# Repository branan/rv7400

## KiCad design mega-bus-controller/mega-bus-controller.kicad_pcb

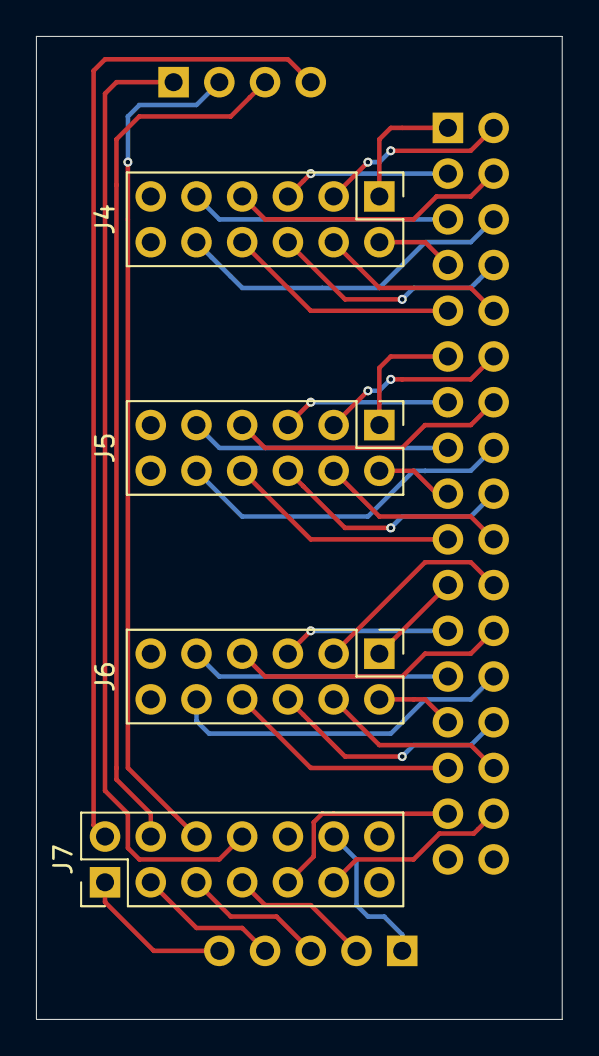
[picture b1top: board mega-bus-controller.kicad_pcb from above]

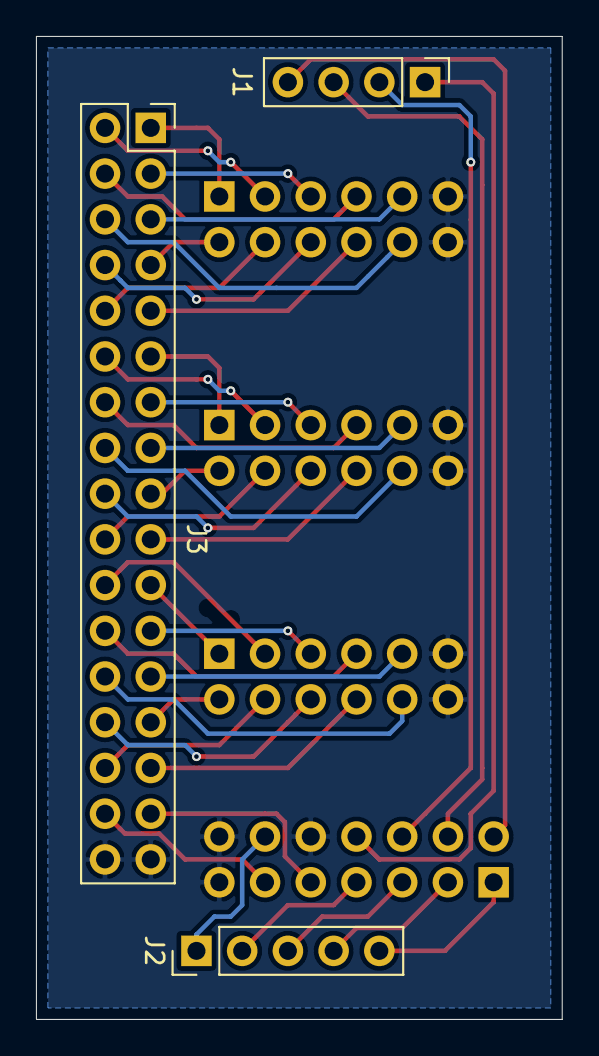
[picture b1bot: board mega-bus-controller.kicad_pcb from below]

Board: 2 copper layers, 29.2 x 54.6 mm, 7 parts (3 on the bottom side), 42 nets.

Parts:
J1: Conn_01x04; PinHeader_1x04_P2.54mm_Vertical
J2: Conn_01x05; PinHeader_1x05_P2.54mm_Vertical
J3: Conn_02x17_Odd_Even; PinHeader_2x17_P2.54mm_Vertical
J4, J5, J6: Conn_02x06_Odd_Even; PinHeader_2x06_P2.54mm_Vertical
J7: Conn_02x07_Odd_Even; PinHeader_2x07_P2.54mm_Vertical

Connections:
/AR0: J3.1, J4.1
/AR1: J3.2, J4.3
/AR2: J3.3, J4.5
/AR3: J3.4, J4.7
/AR4: J3.5, J4.9
/BR0: J3.11, J5.1
/BR1: J3.12, J5.3
/BR2: J3.13, J5.5
/BR3: J3.14, J5.7
/BR4: J3.15, J5.9
/CLK: J2.1, J7.12
/CLK_A: J3.8, J4.6
/CLK_B: J3.18, J5.6
/CLK_Y: J3.28, J6.6
/CTRL_A6: J1.2, J7.6
/CTRL_B5: J1.1, J7.8
/CTRL_B6: J1.3, J7.4
/CTRL_B22: J1.4, J7.2
/DIN_A: J3.6, J4.10
/DIN_B: J3.16, J5.10
/DIN_Y: J3.26, J6.10
/DOUT_A: J3.7, J4.2
/DOUT_B: J3.17, J5.2
/DOUT_Y: J3.27, J6.2
/FUNC0: J2.5, J7.1
/FUNC1: J2.4, J7.3
/FUNC2: J2.3, J7.5
/IMM10: J2.2, J7.7
/MR: J3.31, J7.9
/MW: J3.32, J7.11
/YR0: J3.21, J6.1
/YR1: J3.22, J6.3
/YR2: J3.23, J6.5
/YR3: J3.24, J6.7
/YR4: J3.25, J6.9
/~OE_A: J3.9, J4.8
/~OE_B: J3.19, J5.8
/~OE_Y: J3.29, J6.8
/~SHIFT_A~|LOAD_A: J3.10, J4.4
/~SHIFT_B~|LOAD_B: J3.20, J5.4
/~SHIFT_Y~|LOAD_Y: J3.30, J6.4
GND: J3.33, J3.34, J4.11, J4.12, J5.11, J5.12, J6.11, J6.12, J7.10, J7.13, J7.14

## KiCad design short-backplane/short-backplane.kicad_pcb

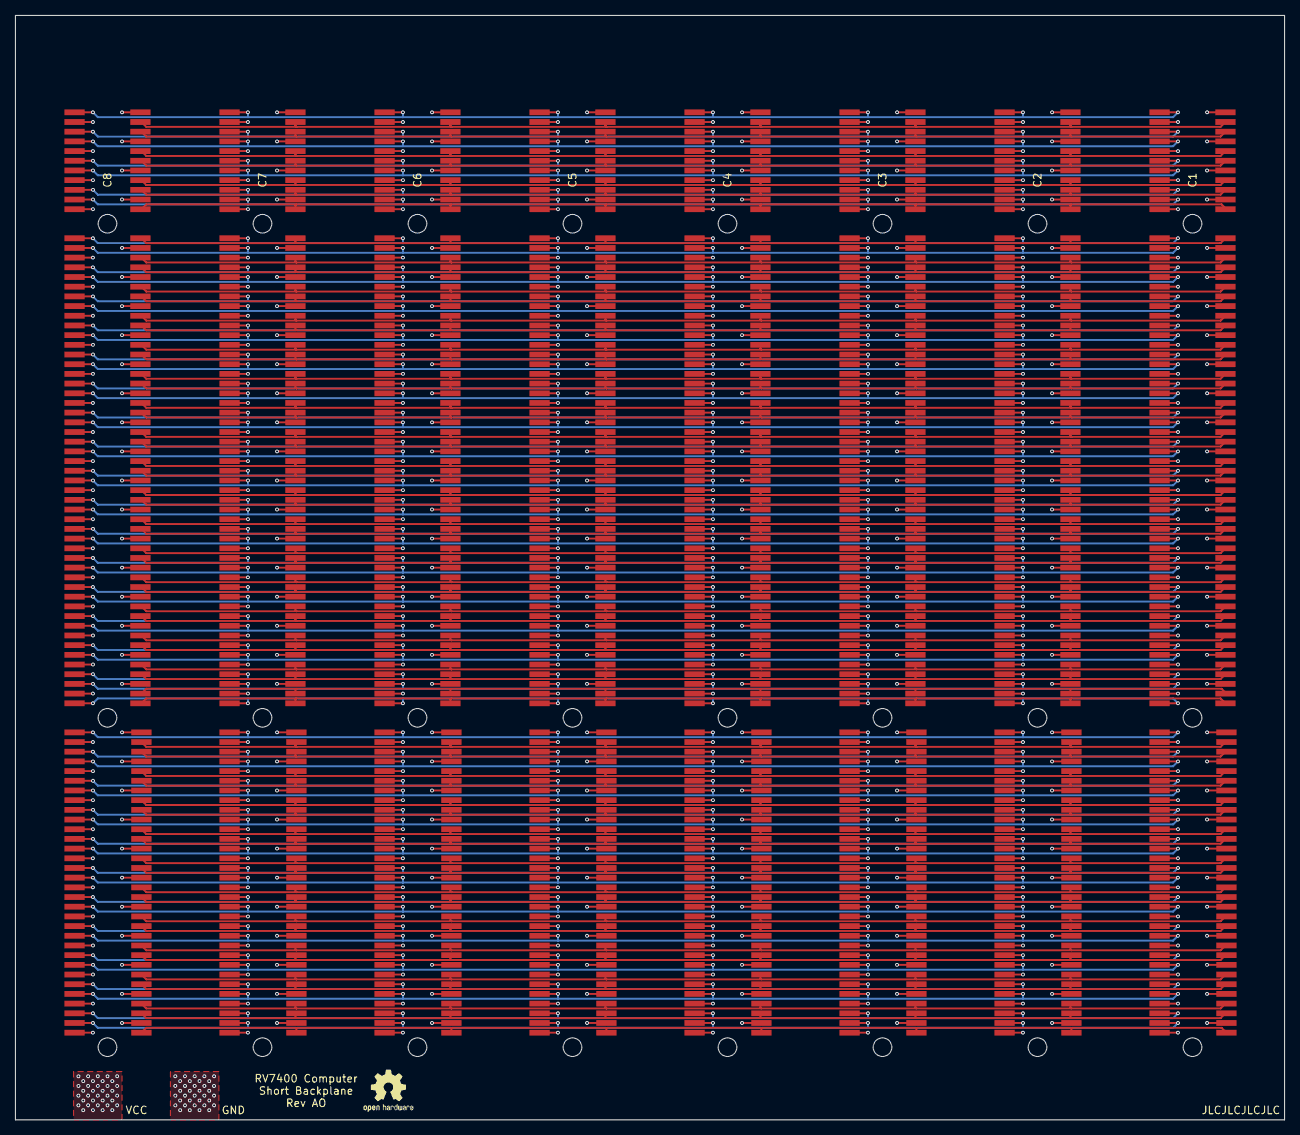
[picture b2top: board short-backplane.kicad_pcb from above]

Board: 4 copper layers, 166.4 x 144.8 mm, 8 parts (0 on the bottom side), 124 nets.

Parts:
C1, C2, C3, C4, C5, C6, C7, C8: Bus; PCI-X Backplane

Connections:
/A0: C1.A23, C2.A23, C3.A23, C4.A23, C5.A23, C6.A23, C7.A23, C8.A23
/A1: C1.B23, C2.B23, C3.B23, C4.B23, C5.B23, C6.B23, C7.B23, C8.B23
/A2: C1.A24, C2.A24, C3.A24, C4.A24, C5.A24, C6.A24, C7.A24, C8.A24
/A3: C1.B25, C2.B25, C3.B25, C4.B25, C5.B25, C6.B25, C7.B25, C8.B25
/A4: C1.A26, C2.A26, C3.A26, C4.A26, C5.A26, C6.A26, C7.A26, C8.A26
/A5: C1.B26, C2.B26, C3.B26, C4.B26, C5.B26, C6.B26, C7.B26, C8.B26
/A6: C1.A27, C2.A27, C3.A27, C4.A27, C5.A27, C6.A27, C7.A27, C8.A27
/A7: C1.B28, C2.B28, C3.B28, C4.B28, C5.B28, C6.B28, C7.B28, C8.B28
/A8: C1.A29, C2.A29, C3.A29, C4.A29, C5.A29, C6.A29, C7.A29, C8.A29
/A9: C1.B29, C2.B29, C3.B29, C4.B29, C5.B29, C6.B29, C7.B29, C8.B29
/A10: C1.A30, C2.A30, C3.A30, C4.A30, C5.A30, C6.A30, C7.A30, C8.A30
/A11: C1.B31, C2.B31, C3.B31, C4.B31, C5.B31, C6.B31, C7.B31, C8.B31
/A12: C1.A32, C2.A32, C3.A32, C4.A32, C5.A32, C6.A32, C7.A32, C8.A32
/A13: C1.B32, C2.B32, C3.B32, C4.B32, C5.B32, C6.B32, C7.B32, C8.B32
/A14: C1.A33, C2.A33, C3.A33, C4.A33, C5.A33, C6.A33, C7.A33, C8.A33
/A15: C1.B34, C2.B34, C3.B34, C4.B34, C5.B34, C6.B34, C7.B34, C8.B34
/A16: C1.A35, C2.A35, C3.A35, C4.A35, C5.A35, C6.A35, C7.A35, C8.A35
/A17: C1.B35, C2.B35, C3.B35, C4.B35, C5.B35, C6.B35, C7.B35, C8.B35
/A18: C1.A36, C2.A36, C3.A36, C4.A36, C5.A36, C6.A36, C7.A36, C8.A36
/A19: C1.B37, C2.B37, C3.B37, C4.B37, C5.B37, C6.B37, C7.B37, C8.B37
/A20: C1.A38, C2.A38, C3.A38, C4.A38, C5.A38, C6.A38, C7.A38, C8.A38
/A21: C1.B38, C2.B38, C3.B38, C4.B38, C5.B38, C6.B38, C7.B38, C8.B38
/A22: C1.A39, C2.A39, C3.A39, C4.A39, C5.A39, C6.A39, C7.A39, C8.A39
/A23: C1.B40, C2.B40, C3.B40, C4.B40, C5.B40, C6.B40, C7.B40, C8.B40
/A24: C1.A41, C2.A41, C3.A41, C4.A41, C5.A41, C6.A41, C7.A41, C8.A41
/A25: C1.B41, C2.B41, C3.B41, C4.B41, C5.B41, C6.B41, C7.B41, C8.B41
/A26: C1.A42, C2.A42, C3.A42, C4.A42, C5.A42, C6.A42, C7.A42, C8.A42
/A27: C1.B43, C2.B43, C3.B43, C4.B43, C5.B43, C6.B43, C7.B43, C8.B43
/A28: C1.A44, C2.A44, C3.A44, C4.A44, C5.A44, C6.A44, C7.A44, C8.A44
/A29: C1.B44, C2.B44, C3.B44, C4.B44, C5.B44, C6.B44, C7.B44, C8.B44
/A30: C1.A45, C2.A45, C3.A45, C4.A45, C5.A45, C6.A45, C7.A45, C8.A45
/A31: C1.B46, C2.B46, C3.B46, C4.B46, C5.B46, C6.B46, C7.B46, C8.B46
/AR0: C1.A1, C2.A1, C3.A1, C4.A1, C5.A1, C6.A1, C7.A1, C8.A1
/AR1: C1.B2, C2.B2, C3.B2, C4.B2, C5.B2, C6.B2, C7.B2, C8.B2
/AR2: C1.A3, C2.A3, C3.A3, C4.A3, C5.A3, C6.A3, C7.A3, C8.A3
/AR3: C1.B3, C2.B3, C3.B3, C4.B3, C5.B3, C6.B3, C7.B3, C8.B3
/AR4: C1.A4, C2.A4, C3.A4, C4.A4, C5.A4, C6.A4, C7.A4, C8.A4
/B0: C1.A47, C2.A47, C3.A47, C4.A47, C5.A47, C6.A47, C7.A47, C8.A47
/B1: C1.B47, C2.B47, C3.B47, C4.B47, C5.B47, C6.B47, C7.B47, C8.B47
/B2: C1.A48, C2.A48, C3.A48, C4.A48, C5.A48, C6.A48, C7.A48, C8.A48
/B3: C1.B49, C2.B49, C3.B49, C4.B49, C5.B49, C6.B49, C7.B49, C8.B49
/B4: C1.A50, C2.A50, C3.A50, C4.A50, C5.A50, C6.A50, C7.A50, C8.A50
/B5: C1.B50, C2.B50, C3.B50, C4.B50, C5.B50, C6.B50, C7.B50, C8.B50
/B6: C1.A51, C2.A51, C3.A51, C4.A51, C5.A51, C6.A51, C7.A51, C8.A51
/B7: C1.B52, C2.B52, C3.B52, C4.B52, C5.B52, C6.B52, C7.B52, C8.B52
/B8: C1.A53, C2.A53, C3.A53, C4.A53, C5.A53, C6.A53, C7.A53, C8.A53
/B9: C1.B53, C2.B53, C3.B53, C4.B53, C5.B53, C6.B53, C7.B53, C8.B53
/B10: C1.A54, C2.A54, C3.A54, C4.A54, C5.A54, C6.A54, C7.A54, C8.A54
/B11: C1.B55, C2.B55, C3.B55, C4.B55, C5.B55, C6.B55, C7.B55, C8.B55
/B12: C1.A56, C2.A56, C3.A56, C4.A56, C5.A56, C6.A56, C7.A56, C8.A56
/B13: C1.B56, C2.B56, C3.B56, C4.B56, C5.B56, C6.B56, C7.B56, C8.B56
/B14: C1.A57, C2.A57, C3.A57, C4.A57, C5.A57, C6.A57, C7.A57, C8.A57
/B15: C1.B58, C2.B58, C3.B58, C4.B58, C5.B58, C6.B58, C7.B58, C8.B58
/B16: C1.A59, C2.A59, C3.A59, C4.A59, C5.A59, C6.A59, C7.A59, C8.A59
/B17: C1.B59, C2.B59, C3.B59, C4.B59, C5.B59, C6.B59, C7.B59, C8.B59
/B18: C1.A60, C2.A60, C3.A60, C4.A60, C5.A60, C6.A60, C7.A60, C8.A60
/B19: C1.B61, C2.B61, C3.B61, C4.B61, C5.B61, C6.B61, C7.B61, C8.B61
/B20: C1.A62, C2.A62, C3.A62, C4.A62, C5.A62, C6.A62, C7.A62, C8.A62
/B21: C1.B62, C2.B62, C3.B62, C4.B62, C5.B62, C6.B62, C7.B62, C8.B62
/B22: C1.A65, C2.A65, C3.A65, C4.A65, C5.A65, C6.A65, C7.A65, C8.A65
/B23: C1.B66, C2.B66, C3.B66, C4.B66, C5.B66, C6.B66, C7.B66, C8.B66
/B24: C1.A67, C2.A67, C3.A67, C4.A67, C5.A67, C6.A67, C7.A67, C8.A67
/B25: C1.B67, C2.B67, C3.B67, C4.B67, C5.B67, C6.B67, C7.B67, C8.B67
/B26: C1.A68, C2.A68, C3.A68, C4.A68, C5.A68, C6.A68, C7.A68, C8.A68
/B27: C1.B69, C2.B69, C3.B69, C4.B69, C5.B69, C6.B69, C7.B69, C8.B69
/B28: C1.A70, C2.A70, C3.A70, C4.A70, C5.A70, C6.A70, C7.A70, C8.A70
/B29: C1.B70, C2.B70, C3.B70, C4.B70, C5.B70, C6.B70, C7.B70, C8.B70
/B30: C1.A71, C2.A71, C3.A71, C4.A71, C5.A71, C6.A71, C7.A71, C8.A71
/B31: C1.B72, C2.B72, C3.B72, C4.B72, C5.B72, C6.B72, C7.B72, C8.B72
/BR0: C1.A7, C2.A7, C3.A7, C4.A7, C5.A7, C6.A7, C7.A7, C8.A7
/BR1: C1.B8, C2.B8, C3.B8, C4.B8, C5.B8, C6.B8, C7.B8, C8.B8
/BR2: C1.A9, C2.A9, C3.A9, C4.A9, C5.A9, C6.A9, C7.A9, C8.A9
/BR3: C1.B9, C2.B9, C3.B9, C4.B9, C5.B9, C6.B9, C7.B9, C8.B9
/BR4: C1.A10, C2.A10, C3.A10, C4.A10, C5.A10, C6.A10, C7.A10, C8.A10
/CLK: C1.B11, C2.B11, C3.B11, C4.B11, C5.B11, C6.B11, C7.B11, C8.B11
/CTRL_A6: C1.A6, C2.A6, C3.A6, C4.A6, C5.A6, C6.A6, C7.A6, C8.A6
/CTRL_B5: C1.B5, C2.B5, C3.B5, C4.B5, C5.B5, C6.B5, C7.B5, C8.B5
/CTRL_B6: C1.B6, C2.B6, C3.B6, C4.B6, C5.B6, C6.B6, C7.B6, C8.B6
/CTRL_B22: C1.B22, C2.B22, C3.B22, C4.B22, C5.B22, C6.B22, C7.B22, C8.B22
/FUNC0: C1.A20, C2.A20, C3.A20, C4.A20, C5.A20, C6.A20, C7.A20, C8.A20
/FUNC1: C1.B20, C2.B20, C3.B20, C4.B20, C5.B20, C6.B20, C7.B20, C8.B20
/FUNC2: C1.A21, C2.A21, C3.A21, C4.A21, C5.A21, C6.A21, C7.A21, C8.A21
/IMM10: C1.B19, C2.B19, C3.B19, C4.B19, C5.B19, C6.B19, C7.B19, C8.B19
/MR: C1.A14, C2.A14, C3.A14, C4.A14, C5.A14, C6.A14, C7.A14, C8.A14
/MW: C1.B14, C2.B14, C3.B14, C4.B14, C5.B14, C6.B14, C7.B14, C8.B14
/Y0: C1.A73, C2.A73, C3.A73, C4.A73, C5.A73, C6.A73, C7.A73, C8.A73
/Y1: C1.B73, C2.B73, C3.B73, C4.B73, C5.B73, C6.B73, C7.B73, C8.B73
/Y2: C1.A74, C2.A74, C3.A74, C4.A74, C5.A74, C6.A74, C7.A74, C8.A74
/Y3: C1.B75, C2.B75, C3.B75, C4.B75, C5.B75, C6.B75, C7.B75, C8.B75
/Y4: C1.A76, C2.A76, C3.A76, C4.A76, C5.A76, C6.A76, C7.A76, C8.A76
/Y5: C1.B76, C2.B76, C3.B76, C4.B76, C5.B76, C6.B76, C7.B76, C8.B76
/Y6: C1.A77, C2.A77, C3.A77, C4.A77, C5.A77, C6.A77, C7.A77, C8.A77
/Y7: C1.B78, C2.B78, C3.B78, C4.B78, C5.B78, C6.B78, C7.B78, C8.B78
/Y8: C1.A79, C2.A79, C3.A79, C4.A79, C5.A79, C6.A79, C7.A79, C8.A79
/Y9: C1.B79, C2.B79, C3.B79, C4.B79, C5.B79, C6.B79, C7.B79, C8.B79
/Y10: C1.A80, C2.A80, C3.A80, C4.A80, C5.A80, C6.A80, C7.A80, C8.A80
/Y11: C1.B81, C2.B81, C3.B81, C4.B81, C5.B81, C6.B81, C7.B81, C8.B81
/Y12: C1.A82, C2.A82, C3.A82, C4.A82, C5.A82, C6.A82, C7.A82, C8.A82
/Y13: C1.B82, C2.B82, C3.B82, C4.B82, C5.B82, C6.B82, C7.B82, C8.B82
/Y14: C1.A83, C2.A83, C3.A83, C4.A83, C5.A83, C6.A83, C7.A83, C8.A83
/Y15: C1.B84, C2.B84, C3.B84, C4.B84, C5.B84, C6.B84, C7.B84, C8.B84
/Y16: C1.A85, C2.A85, C3.A85, C4.A85, C5.A85, C6.A85, C7.A85, C8.A85
/Y17: C1.B85, C2.B85, C3.B85, C4.B85, C5.B85, C6.B85, C7.B85, C8.B85
/Y18: C1.A86, C2.A86, C3.A86, C4.A86, C5.A86, C6.A86, C7.A86, C8.A86
/Y19: C1.B87, C2.B87, C3.B87, C4.B87, C5.B87, C6.B87, C7.B87, C8.B87
/Y20: C1.A88, C2.A88, C3.A88, C4.A88, C5.A88, C6.A88, C7.A88, C8.A88
/Y21: C1.B88, C2.B88, C3.B88, C4.B88, C5.B88, C6.B88, C7.B88, C8.B88
/Y22: C1.A89, C2.A89, C3.A89, C4.A89, C5.A89, C6.A89, C7.A89, C8.A89
/Y23: C1.B90, C2.B90, C3.B90, C4.B90, C5.B90, C6.B90, C7.B90, C8.B90
/Y24: C1.A91, C2.A91, C3.A91, C4.A91, C5.A91, C6.A91, C7.A91, C8.A91
/Y25: C1.B91, C2.B91, C3.B91, C4.B91, C5.B91, C6.B91, C7.B91, C8.B91
/Y26: C1.A92, C2.A92, C3.A92, C4.A92, C5.A92, C6.A92, C7.A92, C8.A92
/Y27: C1.B93, C2.B93, C3.B93, C4.B93, C5.B93, C6.B93, C7.B93, C8.B93
/Y28: C1.A94, C2.A94, C3.A94, C4.A94, C5.A94, C6.A94, C7.A94, C8.A94
/Y29: C1.B94, C2.B94, C3.B94, C4.B94, C5.B94, C6.B94, C7.B94, C8.B94
/Y30: C1.A95, C2.A95, C3.A95, C4.A95, C5.A95, C6.A95, C7.A95, C8.A95
/Y31: C1.B96, C2.B96, C3.B96, C4.B96, C5.B96, C6.B96, C7.B96, C8.B96
/YR0: C1.A15, C2.A15, C3.A15, C4.A15, C5.A15, C6.A15, C7.A15, C8.A15
/YR1: C1.B16, C2.B16, C3.B16, C4.B16, C5.B16, C6.B16, C7.B16, C8.B16
/YR2: C1.A17, C2.A17, C3.A17, C4.A17, C5.A17, C6.A17, C7.A17, C8.A17
/YR3: C1.B17, C2.B17, C3.B17, C4.B17, C5.B17, C6.B17, C7.B17, C8.B17
/YR4: C1.A18, C2.A18, C3.A18, C4.A18, C5.A18, C6.A18, C7.A18, C8.A18
GND: C1.A2, C1.A5, C1.A8, C1.A11, C1.A16, C1.A19, C1.A22, C1.A25, C1.A28, C1.A31, C1.A34, C1.A37, C1.A40, C1.A43, C1.A46, C1.A49, C1.A52, C1.A55, C1.A58, C1.A61, C1.A66, C1.A69, C1.A72, C1.A75, C1.A78, C1.A81, C1.A84, C1.A87, C1.A90, C1.A93, C1.A96, C2.A2, C2.A5, C2.A8, C2.A11, C2.A16, C2.A19, C2.A22, C2.A25, C2.A28, C2.A31, C2.A34, C2.A37, C2.A40, C2.A43, C2.A46, C2.A49, C2.A52, C2.A55, C2.A58, C2.A61, C2.A66, C2.A69, C2.A72, C2.A75, C2.A78, C2.A81, C2.A84, C2.A87, C2.A90, C2.A93, C2.A96, C3.A2, C3.A5, C3.A8, C3.A11, C3.A16, C3.A19, C3.A22, C3.A25, C3.A28, C3.A31, C3.A34, C3.A37, C3.A40, C3.A43, C3.A46, C3.A49, C3.A52, C3.A55, C3.A58, C3.A61, C3.A66, C3.A69, C3.A72, C3.A75, C3.A78, C3.A81, C3.A84, C3.A87, C3.A90, C3.A93, C3.A96, C4.A2, C4.A5, C4.A8, C4.A11, C4.A16, C4.A19, C4.A22, C4.A25, C4.A28, C4.A31, C4.A34, C4.A37, C4.A40, C4.A43, C4.A46, C4.A49, C4.A52, C4.A55, C4.A58, C4.A61, C4.A66, C4.A69, C4.A72, C4.A75, C4.A78, C4.A81, C4.A84, C4.A87, C4.A90, C4.A93, C4.A96, C5.A2, C5.A5, C5.A8, C5.A11, C5.A16, C5.A19, C5.A22, C5.A25, C5.A28, C5.A31, C5.A34, C5.A37, C5.A40, C5.A43, C5.A46, C5.A49, C5.A52, C5.A55, C5.A58, C5.A61, C5.A66, C5.A69, C5.A72, C5.A75, C5.A78, C5.A81, C5.A84, C5.A87, C5.A90, C5.A93, C5.A96, C6.A2, C6.A5, C6.A8, C6.A11, C6.A16, C6.A19, C6.A22, C6.A25, C6.A28, C6.A31, C6.A34, C6.A37, C6.A40, C6.A43, C6.A46, C6.A49, C6.A52, C6.A55, C6.A58, C6.A61, C6.A66, C6.A69, C6.A72, C6.A75, C6.A78, C6.A81, C6.A84, C6.A87, C6.A90, C6.A93, C6.A96, C7.A2, C7.A5, C7.A8, C7.A11, C7.A16, C7.A19, C7.A22, C7.A25, C7.A28, C7.A31, C7.A34, C7.A37, C7.A40, C7.A43, C7.A46, C7.A49, C7.A52, C7.A55, C7.A58, C7.A61, C7.A66, C7.A69, C7.A72, C7.A75, C7.A78, C7.A81, C7.A84, C7.A87, C7.A90, C7.A93, C7.A96, C8.A2, C8.A5, C8.A8, C8.A11, C8.A16, C8.A19, C8.A22, C8.A25, C8.A28, C8.A31, C8.A34, C8.A37, C8.A40, C8.A43, C8.A46, C8.A49, C8.A52, C8.A55, C8.A58, C8.A61, C8.A66, C8.A69, C8.A72, C8.A75, C8.A78, C8.A81, C8.A84, C8.A87, C8.A90, C8.A93, C8.A96
VCC: C1.B1, C1.B4, C1.B7, C1.B10, C1.B15, C1.B18, C1.B21, C1.B24, C1.B27, C1.B30, C1.B33, C1.B36, C1.B39, C1.B42, C1.B45, C1.B48, C1.B51, C1.B54, C1.B57, C1.B60, C1.B65, C1.B68, C1.B71, C1.B74, C1.B77, C1.B80, C1.B83, C1.B86, C1.B89, C1.B92, C1.B95, C2.B1, C2.B4, C2.B7, C2.B10, C2.B15, C2.B18, C2.B21, C2.B24, C2.B27, C2.B30, C2.B33, C2.B36, C2.B39, C2.B42, C2.B45, C2.B48, C2.B51, C2.B54, C2.B57, C2.B60, C2.B65, C2.B68, C2.B71, C2.B74, C2.B77, C2.B80, C2.B83, C2.B86, C2.B89, C2.B92, C2.B95, C3.B1, C3.B4, C3.B7, C3.B10, C3.B15, C3.B18, C3.B21, C3.B24, C3.B27, C3.B30, C3.B33, C3.B36, C3.B39, C3.B42, C3.B45, C3.B48, C3.B51, C3.B54, C3.B57, C3.B60, C3.B65, C3.B68, C3.B71, C3.B74, C3.B77, C3.B80, C3.B83, C3.B86, C3.B89, C3.B92, C3.B95, C4.B1, C4.B4, C4.B7, C4.B10, C4.B15, C4.B18, C4.B21, C4.B24, C4.B27, C4.B30, C4.B33, C4.B36, C4.B39, C4.B42, C4.B45, C4.B48, C4.B51, C4.B54, C4.B57, C4.B60, C4.B65, C4.B68, C4.B71, C4.B74, C4.B77, C4.B80, C4.B83, C4.B86, C4.B89, C4.B92, C4.B95, C5.B1, C5.B4, C5.B7, C5.B10, C5.B15, C5.B18, C5.B21, C5.B24, C5.B27, C5.B30, C5.B33, C5.B36, C5.B39, C5.B42, C5.B45, C5.B48, C5.B51, C5.B54, C5.B57, C5.B60, C5.B65, C5.B68, C5.B71, C5.B74, C5.B77, C5.B80, C5.B83, C5.B86, C5.B89, C5.B92, C5.B95, C6.B1, C6.B4, C6.B7, C6.B10, C6.B15, C6.B18, C6.B21, C6.B24, C6.B27, C6.B30, C6.B33, C6.B36, C6.B39, C6.B42, C6.B45, C6.B48, C6.B51, C6.B54, C6.B57, C6.B60, C6.B65, C6.B68, C6.B71, C6.B74, C6.B77, C6.B80, C6.B83, C6.B86, C6.B89, C6.B92, C6.B95, C7.B1, C7.B4, C7.B7, C7.B10, C7.B15, C7.B18, C7.B21, C7.B24, C7.B27, C7.B30, C7.B33, C7.B36, C7.B39, C7.B42, C7.B45, C7.B48, C7.B51, C7.B54, C7.B57, C7.B60, C7.B65, C7.B68, C7.B71, C7.B74, C7.B77, C7.B80, C7.B83, C7.B86, C7.B89, C7.B92, C7.B95, C8.B1, C8.B4, C8.B7, C8.B10, C8.B15, C8.B18, C8.B21, C8.B24, C8.B27, C8.B30, C8.B33, C8.B36, C8.B39, C8.B42, C8.B45, C8.B48, C8.B51, C8.B54, C8.B57, C8.B60, C8.B65, C8.B68, C8.B71, C8.B74, C8.B77, C8.B80, C8.B83, C8.B86, C8.B89, C8.B92, C8.B95

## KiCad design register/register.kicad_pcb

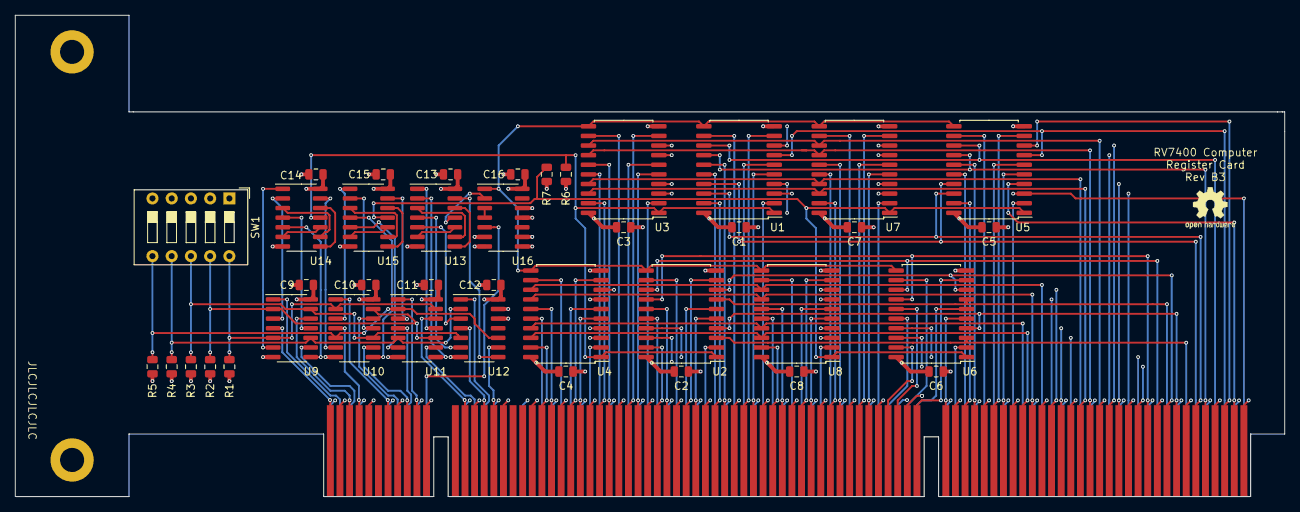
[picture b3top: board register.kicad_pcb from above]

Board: 4 copper layers, 167.6 x 63.6 mm, 41 parts (0 on the bottom side), 148 nets.

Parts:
C1, C2, C3, C4, C5, C6, C7, C8, C9, C10, C11, C12, C13, C14, C15, C16: 100nF; C_0805_2012Metric
R1, R2, R3, R4, R5, R6, R7: 10K; R_0805_2012Metric
SW1: SW_DIP_x05; SW_DIP_SPSTx05_Slide_9.78x14.88mm_W7.62mm_P2.54mm
U1, U2, U3, U4, U5, U6, U7, U8: 74AHC374; SOIC-20W_7.5x12.8mm_P1.27mm
U9, U10, U11, U12: 74AHC86; SOIC-14_3.9x8.7mm_P1.27mm
U13, U14, U15: 74AHC32; SOIC-14_3.9x8.7mm_P1.27mm
U16: 74AHC02; SOIC-14_3.9x8.7mm_P1.27mm
Z1: Bus; PCI-X

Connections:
/A0: U4.19, Z1.A23
/A1: U4.16, Z1.B23
/A2: U4.15, Z1.A24
/A3: U4.12, Z1.B25
/A4: U4.9, Z1.A26
/A5: U4.6, Z1.B26
/A6: U4.5, Z1.A27
/A7: U4.2, Z1.B28
/A8: U3.19, Z1.A29
/A9: U3.16, Z1.B29
/A10: U3.15, Z1.A30
/A11: U3.12, Z1.B31
/A12: U3.9, Z1.A32
/A13: U3.6, Z1.B32
/A14: U3.5, Z1.A33
/A15: U3.2, Z1.B34
/A16: U2.19, Z1.A35
/A17: U2.16, Z1.B35
/A18: U2.15, Z1.A36
/A19: U2.12, Z1.B37
/A20: U2.9, Z1.A38
/A21: U2.6, Z1.B38
/A22: U2.5, Z1.A39
/A23: U2.2, Z1.B40
/A24: U1.19, Z1.A41
/A25: U1.16, Z1.B41
/A26: U1.15, Z1.A42
/A27: U1.12, Z1.B43
/A28: U1.9, Z1.A44
/A29: U1.6, Z1.B44
/A30: U1.5, Z1.A45
/A31: U1.2, Z1.B46
/AR0: U9.4, Z1.A1
/AR1: U9.1, Z1.B2
/AR2: U9.12, Z1.A3
/AR3: U9.9, Z1.B3
/AR4: U10.4, Z1.A4
/B0: U8.19, Z1.A47
/B1: U8.16, Z1.B47
/B2: U8.15, Z1.A48
/B3: U8.12, Z1.B49
/B4: U8.9, Z1.A50
/B5: U8.6, Z1.B50
/B6: U8.5, Z1.A51
/B7: U8.2, Z1.B52
/B8: U7.19, Z1.A53
/B9: U7.16, Z1.B53
/B10: U7.15, Z1.A54
/B11: U7.12, Z1.B55
/B12: U7.9, Z1.A56
/B13: U7.6, Z1.B56
/B14: U7.5, Z1.A57
/B15: U7.2, Z1.B58
/B16: U6.19, Z1.A59
/B17: U6.16, Z1.B59
/B18: U6.15, Z1.A60
/B19: U6.12, Z1.B61
/B20: U6.9, Z1.A62
/B21: U6.6, Z1.B62
/B22: U6.5, Z1.A65
/B23: U6.2, Z1.B66
/B24: U5.19, Z1.A67
/B25: U5.16, Z1.B67
/B26: U5.15, Z1.A68
/B27: U5.12, Z1.B69
/B28: U5.9, Z1.A70
/B29: U5.6, Z1.B70
/B30: U5.5, Z1.A71
/B31: U5.2, Z1.B72
/BR0: U10.1, Z1.A7
/BR1: U10.12, Z1.B8
/BR2: U10.9, Z1.A9
/BR3: U11.4, Z1.B9
/BR4: U11.1, Z1.A10
/CLK: U1.11, U2.11, U3.11, U4.11, U5.11, U6.11, U7.11, U8.11, U16.1
/CLKIN: U16.5, Z1.B11
/Y0: U4.18, U8.18, Z1.A73
/Y1: U4.17, U8.17, Z1.B73
/Y2: U4.14, U8.14, Z1.A74
/Y3: U4.13, U8.13, Z1.B75
/Y4: U4.8, U8.8, Z1.A76
/Y5: U4.7, U8.7, Z1.B76
/Y6: U4.4, U8.4, Z1.A77
/Y7: U4.3, U8.3, Z1.B78
/Y8: U3.18, U7.18, Z1.A79
/Y9: U3.17, U7.17, Z1.B79
/Y10: U3.14, U7.14, Z1.A80
/Y11: U3.13, U7.13, Z1.B81
/Y12: U3.8, U7.8, Z1.A82
/Y13: U3.7, U7.7, Z1.B82
/Y14: U3.4, U7.4, Z1.A83
/Y15: U3.3, U7.3, Z1.B84
/Y16: U2.18, U6.18, Z1.A85
/Y17: U2.17, U6.17, Z1.B85
/Y18: U2.14, U6.14, Z1.A86
/Y19: U2.13, U6.13, Z1.B87
/Y20: U2.8, U6.8, Z1.A88
/Y21: U2.7, U6.7, Z1.B88
/Y22: U2.4, U6.4, Z1.A89
/Y23: U2.3, U6.3, Z1.B90
/Y24: U1.18, U5.18, Z1.A91
/Y25: U1.17, U5.17, Z1.B91
/Y26: U1.14, U5.14, Z1.A92
/Y27: U1.13, U5.13, Z1.B93
/Y28: U1.8, U5.8, Z1.A94
/Y29: U1.7, U5.7, Z1.B94
/Y30: U1.4, U5.4, Z1.A95
/Y31: U1.3, U5.3, Z1.B96
/YR0: U11.12, Z1.A15
/YR1: U11.9, Z1.B16
/YR2: U12.4, Z1.A17
/YR3: U12.1, Z1.B17
/YR4: U12.9, Z1.A18
/~AE: R6.2, U1.1, U2.1, U3.1, U4.1, U14.11
/~BE: R7.2, U5.1, U6.1, U7.1, U8.1, U15.11
/~YE: U13.11, U16.2
GND: C1.2, C2.2, C3.2, C4.2, C5.2, C6.2, C7.2, C8.2, C9.2, C10.2, C11.2, C12.2, C13.2, C14.2, C15.2, C16.2, R1.2, R2.2, R3.2, R4.2, R5.2, U1.10, U2.10, U3.10, U4.10, U5.10, U6.10, U7.10, U8.10, U9.7, U10.7, U11.7, U12.7, U12.12, U12.13, U13.7, U14.7, U15.7, U16.6, U16.7, U16.8, U16.9, U16.11, U16.12, Z1.A2, Z1.A5, Z1.A8, Z1.A11, Z1.A16, Z1.A19, Z1.A22, Z1.A25, Z1.A28, Z1.A31, Z1.A34, Z1.A37, Z1.A40, Z1.A43, Z1.A46, Z1.A49, Z1.A52, Z1.A55, Z1.A58, Z1.A61, Z1.A66, Z1.A69, Z1.A72, Z1.A75, Z1.A78, Z1.A81, Z1.A84, Z1.A87, Z1.A90, Z1.A93, Z1.A96
unnamed: R1.1, SW1.10, U9.5, U10.2, U11.13
unnamed: R2.1, SW1.9, U9.2, U10.13, U11.10
unnamed: R3.1, SW1.8, U9.13, U10.10, U12.5
unnamed: R4.1, SW1.7, U9.10, U11.5, U12.2
unnamed: R5.1, SW1.6, U10.5, U11.2, U12.10
unnamed: U10.3, U15.1
unnamed: U10.6, U14.13
unnamed: U10.8, U15.4
unnamed: U10.11, U15.2
unnamed: U11.3, U15.13
unnamed: U11.6, U15.5
unnamed: U11.8, U13.2
unnamed: U11.11, U13.1
unnamed: U12.3, U13.5
unnamed: U12.6, U13.4
unnamed: U12.8, U13.13
unnamed: U13.3, U13.9
unnamed: U13.6, U13.10
unnamed: U13.8, U13.12
unnamed: U9.6, U14.1
unnamed: U9.3, U14.2
unnamed: U14.3, U14.9
unnamed: U9.11, U14.4
unnamed: U9.8, U14.5
unnamed: U14.6, U14.10
unnamed: U14.8, U14.12
unnamed: U15.3, U15.9
unnamed: U15.6, U15.10
unnamed: U15.8, U15.12
unnamed: U16.3, U16.4
VCC: C1.1, C2.1, C3.1, C4.1, C5.1, C6.1, C7.1, C8.1, C9.1, C10.1, C11.1, C12.1, C13.1, C14.1, C15.1, C16.1, R6.1, R7.1, SW1.1, SW1.2, SW1.3, SW1.4, SW1.5, U1.20, U2.20, U3.20, U4.20, U5.20, U6.20, U7.20, U8.20, U9.14, U10.14, U11.14, U12.14, U13.14, U14.14, U15.14, U16.14, Z1.B1, Z1.B4, Z1.B7, Z1.B10, Z1.B15, Z1.B18, Z1.B21, Z1.B24, Z1.B27, Z1.B30, Z1.B33, Z1.B36, Z1.B39, Z1.B42, Z1.B45, Z1.B48, Z1.B51, Z1.B54, Z1.B57, Z1.B60, Z1.B65, Z1.B68, Z1.B71, Z1.B74, Z1.B77, Z1.B80, Z1.B83, Z1.B86, Z1.B89, Z1.B92, Z1.B95

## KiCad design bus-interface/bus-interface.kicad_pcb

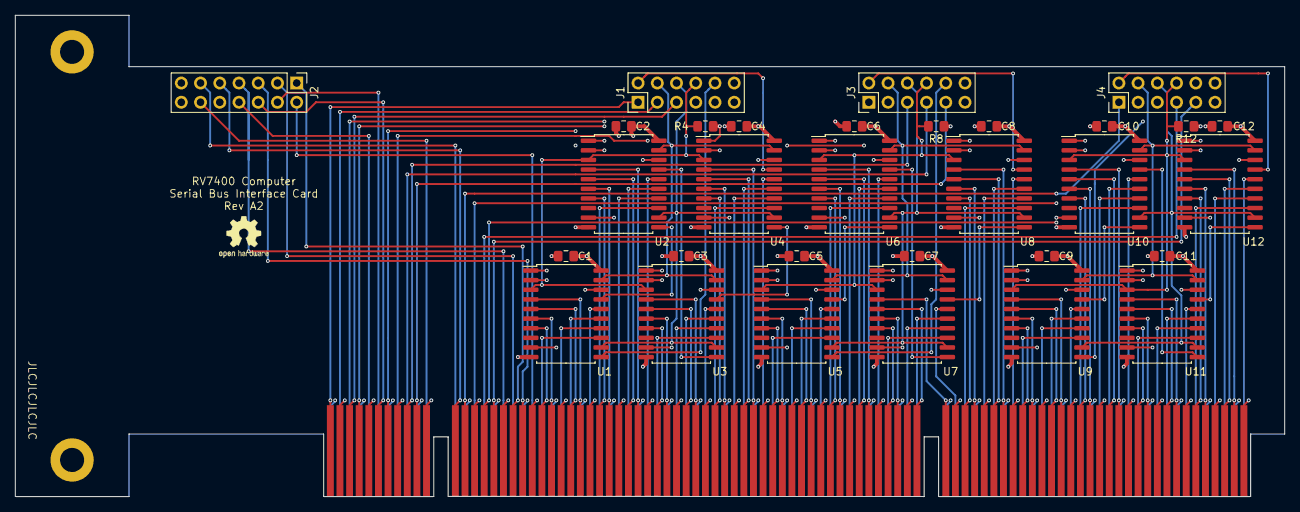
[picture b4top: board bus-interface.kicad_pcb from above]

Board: 4 copper layers, 167.6 x 63.6 mm, 32 parts (0 on the bottom side), 148 nets.

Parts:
C1, C2, C3, C4, C5, C6, C7, C8, C9, C10, C11, C12: 100nF; C_0805_2012Metric_Pad1.15x1.40mm_HandSolder
J1, J3, J4: Conn_02x06_Odd_Even; PinHeader_2x06_P2.54mm_Vertical
J2: Conn_02x07_Odd_Even; PinHeader_2x07_P2.54mm_Vertical
R4, R8, R12: 10K; R_0805_2012Metric_Pad1.15x1.40mm_HandSolder
U1, U2, U3, U4, U5, U6, U7, U8, U9, U10, U11, U12: 74HC299; SOIC-20W_7.5x12.8mm_P1.27mm
Z1: Bus; PCI-X

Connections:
/A0: U1.7, Z1.A23
/A1: U1.13, Z1.B23
/A2: U1.6, Z1.A24
/A3: U1.14, Z1.B25
/A4: U1.5, Z1.A26
/A5: U1.15, Z1.B26
/A6: U1.4, Z1.A27
/A7: U1.16, Z1.B28
/A8: U2.7, Z1.A29
/A9: U2.13, Z1.B29
/A10: U2.6, Z1.A30
/A11: U2.14, Z1.B31
/A12: U2.5, Z1.A32
/A13: U2.15, Z1.B32
/A14: U2.4, Z1.A33
/A15: U2.16, Z1.B34
/A16: U3.7, Z1.A35
/A17: U3.13, Z1.B35
/A18: U3.6, Z1.A36
/A19: U3.14, Z1.B37
/A20: U3.5, Z1.A38
/A21: U3.15, Z1.B38
/A22: U3.4, Z1.A39
/A23: U3.16, Z1.B40
/A24: U4.7, Z1.A41
/A25: U4.13, Z1.B41
/A26: U4.6, Z1.A42
/A27: U4.14, Z1.B43
/A28: U4.5, Z1.A44
/A29: U4.15, Z1.B44
/A30: U4.4, Z1.A45
/A31: U4.16, Z1.B46
/AR0: J1.1, Z1.A1
/AR1: J1.3, Z1.B2
/AR2: J1.5, Z1.A3
/AR3: J1.7, Z1.B3
/AR4: J1.9, Z1.A4
/B0: U5.7, Z1.A47
/B1: U5.13, Z1.B47
/B2: U5.6, Z1.A48
/B3: U5.14, Z1.B49
/B4: U5.5, Z1.A50
/B5: U5.15, Z1.B50
/B6: U5.4, Z1.A51
/B7: U5.16, Z1.B52
/B8: U6.7, Z1.A53
/B9: U6.13, Z1.B53
/B10: U6.6, Z1.A54
/B11: U6.14, Z1.B55
/B12: U6.5, Z1.A56
/B13: U6.15, Z1.B56
/B14: U6.4, Z1.A57
/B15: U6.16, Z1.B58
/B16: U7.7, Z1.A59
/B17: U7.13, Z1.B59
/B18: U7.6, Z1.A60
/B19: U7.14, Z1.B61
/B20: U7.5, Z1.A62
/B21: U7.15, Z1.B62
/B22: U7.4, Z1.A65
/B23: U7.16, Z1.B66
/B24: U8.7, Z1.A67
/B25: U8.13, Z1.B67
/B26: U8.6, Z1.A68
/B27: U8.14, Z1.B69
/B28: U8.5, Z1.A70
/B29: U8.15, Z1.B70
/B30: U8.4, Z1.A71
/B31: U8.16, Z1.B72
/BR0: J3.1, Z1.A7
/BR1: J3.3, Z1.B8
/BR2: J3.5, Z1.A9
/BR3: J3.7, Z1.B9
/BR4: J3.9, Z1.A10
/CLK: J2.12, Z1.B11
/CLK_A: J1.6, U1.12, U2.12, U3.12, U4.12
/CLK_B: J3.6, U5.12, U6.12, U7.12, U8.12
/CLK_Y: J4.6, U9.12, U10.12, U11.12, U12.12
/CTRL_A6: J2.6, Z1.A6
/CTRL_B5: J2.8, Z1.B5
/CTRL_B6: J2.4, Z1.B6
/CTRL_B22: J2.2, Z1.B22
/DIN_A: J1.10, U1.11
/DIN_B: J3.10, U5.11
/DIN_Y: J4.10, U9.11
/DOUT_A: J1.2, U4.17
/DOUT_B: J3.2, U8.17
/DOUT_Y: J4.2, U12.17
/FUNC0: J2.1, Z1.A20
/FUNC1: J2.3, Z1.B20
/FUNC2: J2.5, Z1.A21
/IMM10: J2.7, Z1.B19
/MR: J2.9, Z1.A14
/MW: J2.11, Z1.B14
/Y0: U9.7, Z1.A73
/Y1: U9.13, Z1.B73
/Y2: U9.6, Z1.A74
/Y3: U9.14, Z1.B75
/Y4: U9.5, Z1.A76
/Y5: U9.15, Z1.B76
/Y6: U9.4, Z1.A77
/Y7: U9.16, Z1.B78
/Y8: U10.7, Z1.A79
/Y9: U10.13, Z1.B79
/Y10: U10.6, Z1.A80
/Y11: U10.14, Z1.B81
/Y12: U10.5, Z1.A82
/Y13: U10.15, Z1.B82
/Y14: U10.4, Z1.A83
/Y15: U10.16, Z1.B84
/Y16: U11.7, Z1.A85
/Y17: U11.13, Z1.B85
/Y18: U11.6, Z1.A86
/Y19: U11.14, Z1.B87
/Y20: U11.5, Z1.A88
/Y21: U11.15, Z1.B88
/Y22: U11.4, Z1.A89
/Y23: U11.16, Z1.B90
/Y24: U12.7, Z1.A91
/Y25: U12.13, Z1.B91
/Y26: U12.6, Z1.A92
/Y27: U12.14, Z1.B93
/Y28: U12.5, Z1.A94
/Y29: U12.15, Z1.B94
/Y30: U12.4, Z1.A95
/Y31: U12.16, Z1.B96
/YR0: J4.1, Z1.A15
/YR1: J4.3, Z1.B16
/YR2: J4.5, Z1.A17
/YR3: J4.7, Z1.B17
/YR4: J4.9, Z1.A18
/~OE_A: J1.8, R4.2, U1.3, U2.3, U3.3, U4.3
/~OE_B: J3.8, R8.2, U5.3, U6.3, U7.3, U8.3
/~OE_Y: J4.8, R12.2, U9.3, U10.3, U11.3, U12.3
/~SHIFT_A~|LOAD_A: J1.4, U1.19, U2.19, U3.19, U4.19
/~SHIFT_B~|LOAD_B: J3.4, U5.19, U6.19, U7.19, U8.19
/~SHIFT_Y~|LOAD_Y: J4.4, U9.19, U10.19, U11.19, U12.19
GND: C1.2, C2.2, C3.2, C4.2, C5.2, C6.2, C7.2, C8.2, C9.2, C10.2, C11.2, C12.2, J1.11, J1.12, J2.10, J2.13, J2.14, J3.11, J3.12, J4.11, J4.12, U1.2, U1.10, U1.18, U2.2, U2.10, U2.18, U3.2, U3.10, U3.18, U4.2, U4.10, U4.18, U5.2, U5.10, U5.18, U6.2, U6.10, U6.18, U7.2, U7.10, U7.18, U8.2, U8.10, U8.18, U9.2, U9.10, U9.18, U10.2, U10.10, U10.18, U11.2, U11.10, U11.18, U12.2, U12.10, U12.18, Z1.A2, Z1.A5, Z1.A8, Z1.A11, Z1.A16, Z1.A19, Z1.A22, Z1.A25, Z1.A28, Z1.A31, Z1.A34, Z1.A37, Z1.A40, Z1.A43, Z1.A46, Z1.A49, Z1.A52, Z1.A55, Z1.A58, Z1.A61, Z1.A66, Z1.A69, Z1.A72, Z1.A75, Z1.A78, Z1.A81, Z1.A84, Z1.A87, Z1.A90, Z1.A93, Z1.A96
unnamed: U1.17, U2.11
unnamed: U2.17, U3.11
unnamed: U3.17, U4.11
unnamed: U5.17, U6.11
unnamed: U6.17, U7.11
unnamed: U7.17, U8.11
unnamed: U9.17, U10.11
unnamed: U10.17, U11.11
unnamed: U11.17, U12.11
VCC: C1.1, C2.1, C3.1, C4.1, C5.1, C6.1, C7.1, C8.1, C9.1, C10.1, C11.1, C12.1, R4.1, R8.1, R12.1, U1.1, U1.9, U1.20, U2.1, U2.9, U2.20, U3.1, U3.9, U3.20, U4.1, U4.9, U4.20, U5.1, U5.9, U5.20, U6.1, U6.9, U6.20, U7.1, U7.9, U7.20, U8.1, U8.9, U8.20, U9.1, U9.9, U9.20, U10.1, U10.9, U10.20, U11.1, U11.9, U11.20, U12.1, U12.9, U12.20, Z1.B1, Z1.B4, Z1.B7, Z1.B10, Z1.B15, Z1.B18, Z1.B21, Z1.B24, Z1.B27, Z1.B30, Z1.B33, Z1.B36, Z1.B39, Z1.B42, Z1.B45, Z1.B48, Z1.B51, Z1.B54, Z1.B57, Z1.B60, Z1.B65, Z1.B68, Z1.B71, Z1.B74, Z1.B77, Z1.B80, Z1.B83, Z1.B86, Z1.B89, Z1.B92, Z1.B95

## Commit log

2019-12-11 Initial import with register
    This is an initial import of the project with the register card and
    the bits necessary to test it.
